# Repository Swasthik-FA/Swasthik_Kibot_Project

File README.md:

<h1 align="center">Board Name</h1>

<p align="center" width="100%">
  
</p>

***

<p align="center">
  
&nbsp; &nbsp; &nbsp; &nbsp;
  
</p>

***

## SPECIFICATIONS

| Parameter | Value | 
| --- | --- |
| Dimensions | 106.58 × 54.37 mm |

***

## DIRECTORY STRUCTURE

    .
    ├─ Computations       # Misc calculations
    ├─ HTML               # HTML files for generated webpage
    ├─ Images             # Pictures and renders
    │
    ├─ kibot_resources    # External resources for KiBot
    │  ├─ colors          # Color theme for KiCad
    │  ├─ fonts           # Fonts used in the project
    │  ├─ scripts         # External scripts used with KiBot
    │  └─ templates       # Templates for KiBot generated reports
    │
    ├─ kibot_yaml         # KiBot YAML config files
    ├─ KiRI               # KiRI (PCB diff viewer) files
    │
    ├─ lib                # KiCad footprint and symbol libraries
    │  ├─ 3d_models       # Component 3D models
    │  ├─ lib_fp          # Footprint libraries
    │  └─ lib_sym         # Symbol libraries
    │
    ├─ Logos              # Logos
    │
    ├─ Manufacturing      # Assembly and fabrication documents
    │  ├─ Assembly        # Assembly documents (BoM, pos, notes)
    │  │
    │  └─ Fabrication     # Fabrication documents (ZIP, notes)
    │     ├─ Drill Tables # CSV drill tables
    │     └─ Gerbers      # Gerbers
    │
    ├─ Report             # Reports for ERC/DRC
    ├─ Schematic          # PDF of schematic
    ├─ Templates          # Title block templates
    ├─ Testing
    │  └─ Testpoints      # Testpoints tables      
    │
    └─ Variants           # Outputs for assembly variants

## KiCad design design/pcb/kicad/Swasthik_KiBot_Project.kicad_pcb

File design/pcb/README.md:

# design/pcb/

This is the main working area for the PCB. Everything related to the circuit board lives under this directory.

See `../../FAQ.md` for the file-location lookup table and detailed Q&A.

## What's pre-created

Only two subdirectories are created by the template:

| Folder | Why it's pre-created |
|---|---|
| `kicad/` | KiCad project files go here. The shell scripts default to `design/pcb/kicad/Swasthik_KiBot_Project.kicad_pro` and related paths. |
| `outputs/` | Scripts write generated reports (ERC, DRC, BOM, schematic PDF) here. CI reads from here. |
| `reviews/` | Completed gate checklists land here as the project progresses through the 5 quality gates. |

## What to create when you need it

Everything else is created on demand. The template deliberately does not pre-materialize empty folders, because most projects will not use all of them. Create these as the work reaches that stage:

| Folder | When to create |
|---|---|
| `kicad/libraries/symbols/` | When you draw your first project-local schematic symbol |
| `kicad/libraries/footprints.pretty/` | When you create your first project-local footprint (note: `.pretty` suffix is mandatory — KiCad convention) |
| `kicad/libraries/3d/` | When you add your first project-local 3D model (STEP, WRL) |
| `datasheets/` | When you add your first component datasheet |
| `notes/` | When you start writing design notes (power tree calc, placement rationale, etc.) |
| `ecos/` | When the first Engineering Change Order happens (after prototype fabrication) |
| `outputs/review_pack/` | When you run `../../scripts/export_review_pack.sh` for the first time |
| `reviews/g1_specification_lock/`, `g2_schematic_review/`, etc. | When each gate is passed and the completed checklist is archived |
| `../mechanical/` | If the project has mechanical constraints (enclosure STEP, DXF) |
| `simulation/` | If you run simulation (LTspice, ngspice) |
| `references/` | If you collect app notes, reference designs, or competitor teardowns |

## The rule

**If a file describes the PCB, it lives under `design/pcb/`.** Source files, libraries, datasheets, generated outputs, review evidence, change orders — all here. The only exceptions are: (1) per-revision release packs at `release/`, and (2) project-level config at the repo root (`project_config.md`, etc.).

## Related files

- `../../README.md` — overall template guide
- `../../FAQ.md` — file-location lookup and Q&A (creating folders on demand is covered in section 2)
- `../../CLAUDE.md` — AI context for this repo

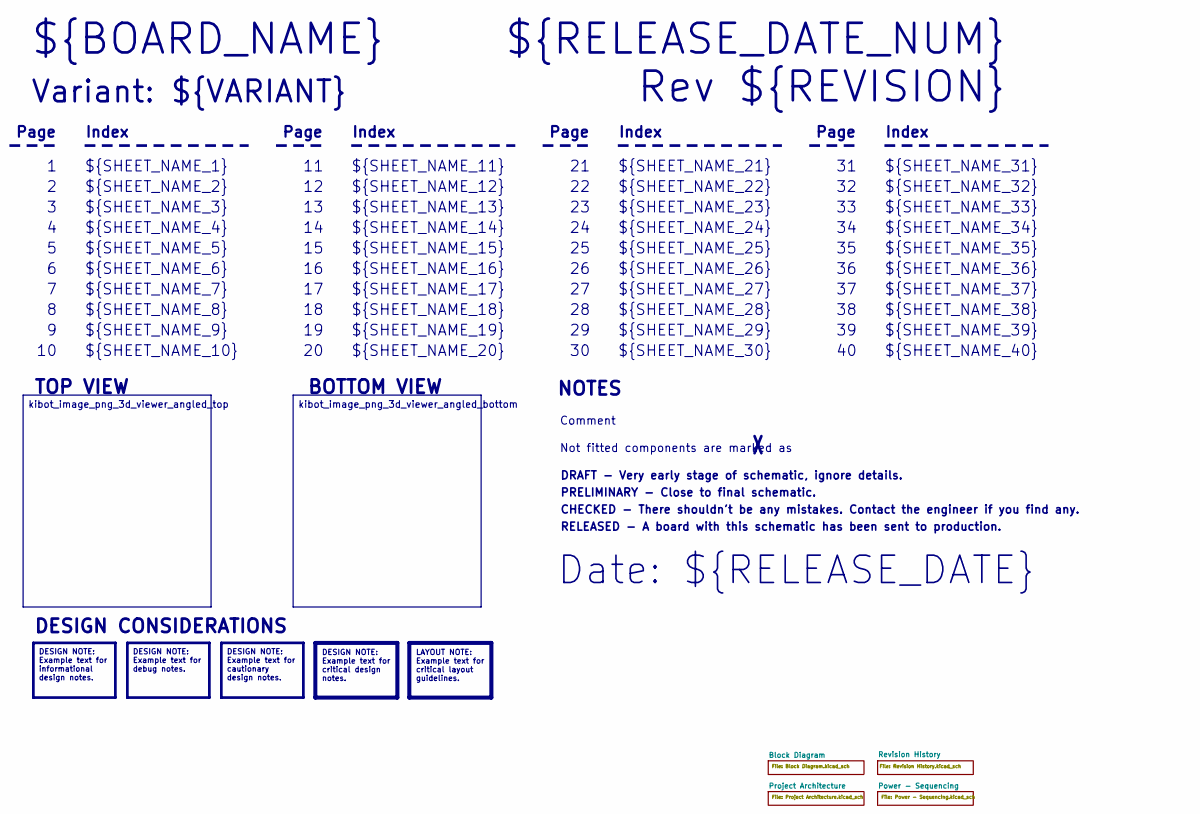
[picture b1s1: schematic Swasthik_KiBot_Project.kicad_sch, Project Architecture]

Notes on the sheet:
Variant: ${VARIANT}
RELEASED - A board with this schematic has been sent to production.
${SHEET_NAME_24}
Index
Page
PRELIMINARY - Close to final schematic.
${SHEET_NAME_22}
DRAFT - Very early stage of schematic, ignore details.
${SHEET_NAME_12}
${SHEET_NAME_8}
${SHEET_NAME_2}
${SHEET_NAME_5}
${SHEET_NAME_20}
${SHEET_NAME_23}
${RELEASE_DATE_NUM}
${SHEET_NAME_35}
Not fitted components are marked as
${SHEET_NAME_11}
${SHEET_NAME_6}
${SHEET_NAME_37}
${SHEET_NAME_26}
${SHEET_NAME_36}
Rev ${REVISION}
${SHEET_NAME_15}
CHECKED - There shouldn't be any mistakes. Contact the engineer if you find any.
BOTTOM VIEW
${SHEET_NAME_14}
${SHEET_NAME_21}
${SHEET_NAME_17}
${SHEET_NAME_18}
Date: ${RELEASE_DATE}
${SHEET_NAME_7}
${SHEET_NAME_31}
${BOARD_NAME}
NOTES
${SHEET_NAME_40}
${SHEET_NAME_39}
${SHEET_NAME_32}
${SHEET_NAME_1}
${SHEET_NAME_9}

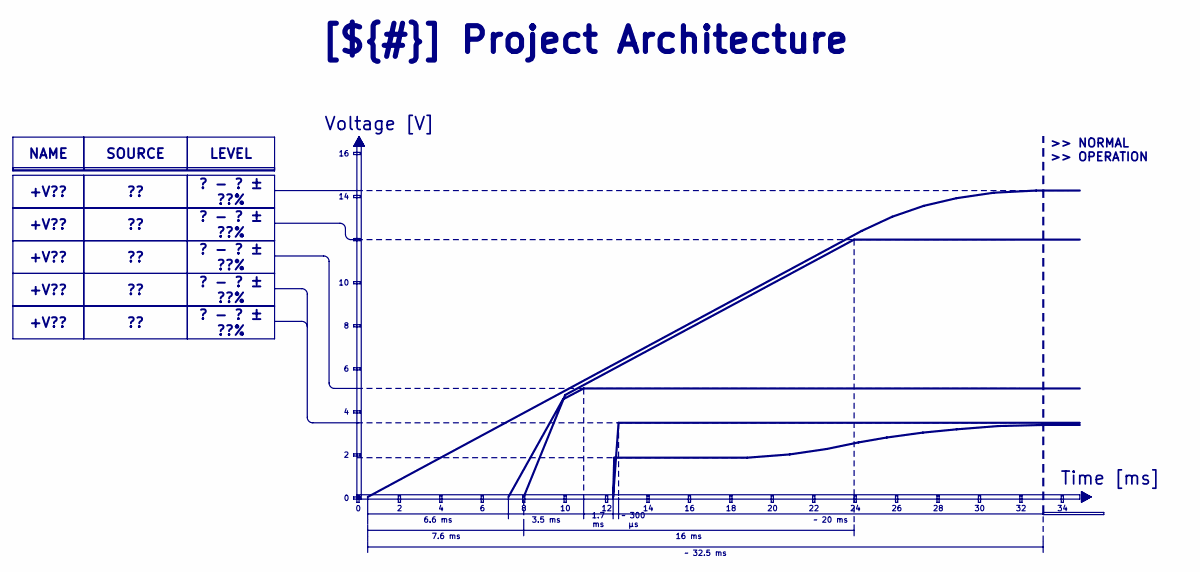
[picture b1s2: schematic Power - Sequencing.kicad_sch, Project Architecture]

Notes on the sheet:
Voltage [V]
>> NORMAL >> OPERATION
Time [ms]
3.5 ms
7.6 ms
? - ? ± ??%
~ 300 μs
1.7 ms
16 ms
+V??
LEVEL
NAME
~ 20 ms
SOURCE
[${#}] ${TITLE}
6.6 ms
~ 32.5 ms

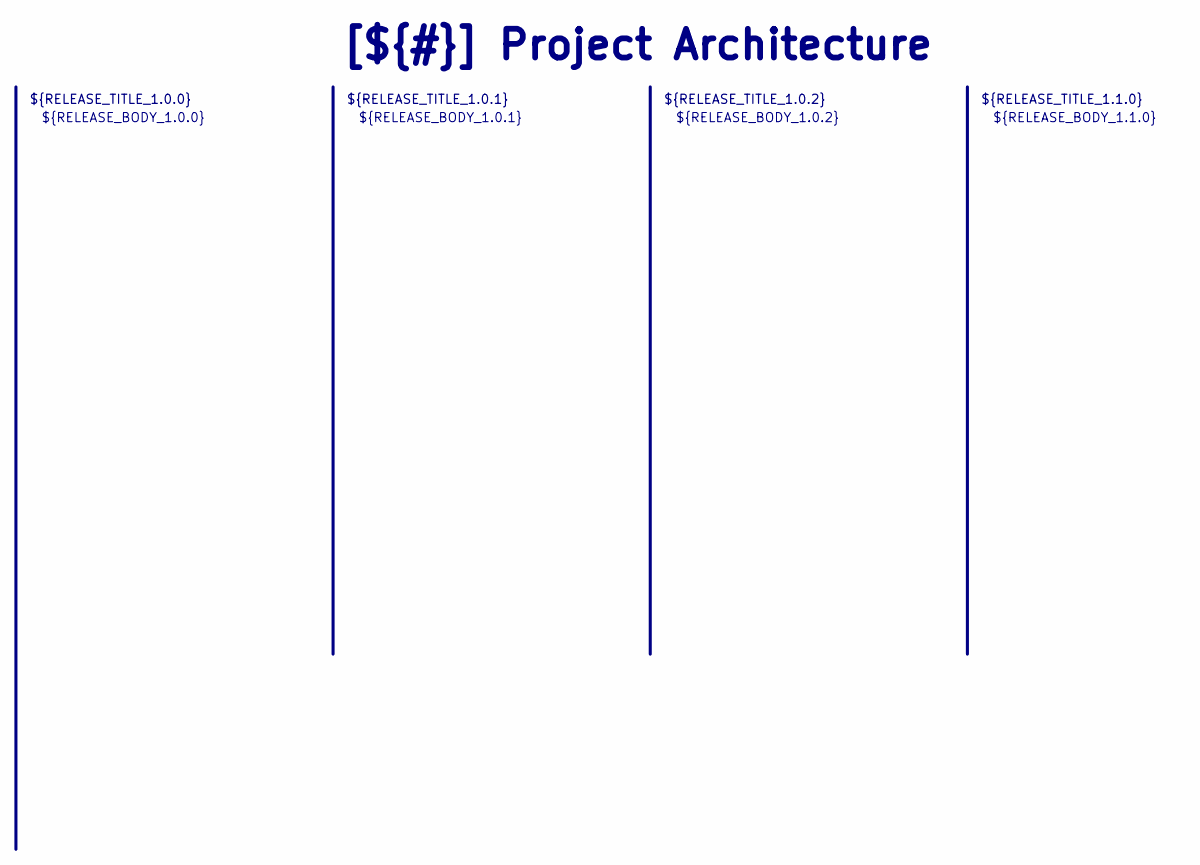
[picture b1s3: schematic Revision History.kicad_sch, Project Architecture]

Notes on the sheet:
${RELEASE_BODY_1.1.0}
[${#}] ${TITLE}
${RELEASE_BODY_1.0.0}
${RELEASE_TITLE_1.0.2}
${RELEASE_BODY_1.0.2}
${RELEASE_BODY_1.0.1}
${RELEASE_TITLE_1.0.0}
${RELEASE_TITLE_1.0.1}
${RELEASE_TITLE_1.1.0}

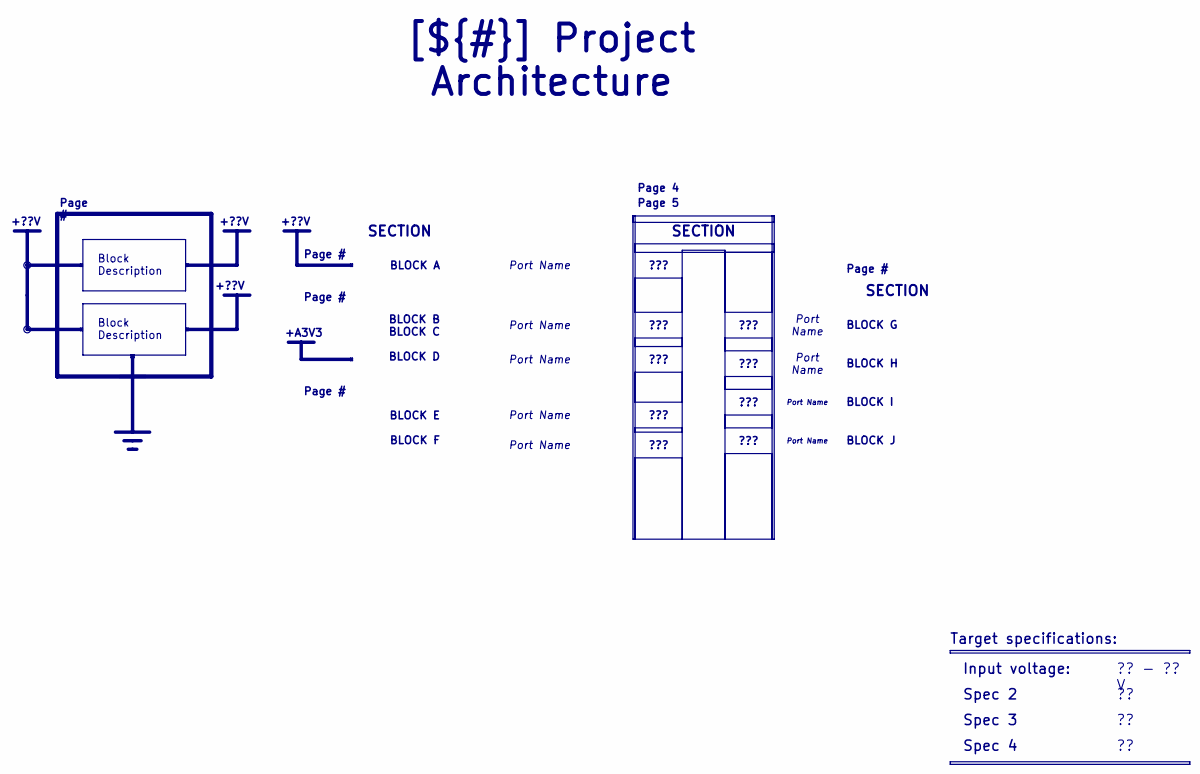
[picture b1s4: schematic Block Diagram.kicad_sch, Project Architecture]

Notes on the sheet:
+??V
+A3V3
SECTION
Spec 4
BLOCK H
BLOCK B BLOCK C BLOCK D
BLOCK I
?? - ?? V
Block Description
???
Port Name
BLOCK G
Page #
Page 4
[${#}] ${TITLE}
Input voltage:
Target specifications:
Spec 3
Spec 2
BLOCK A
BLOCK E BLOCK F
BLOCK J
Page 5

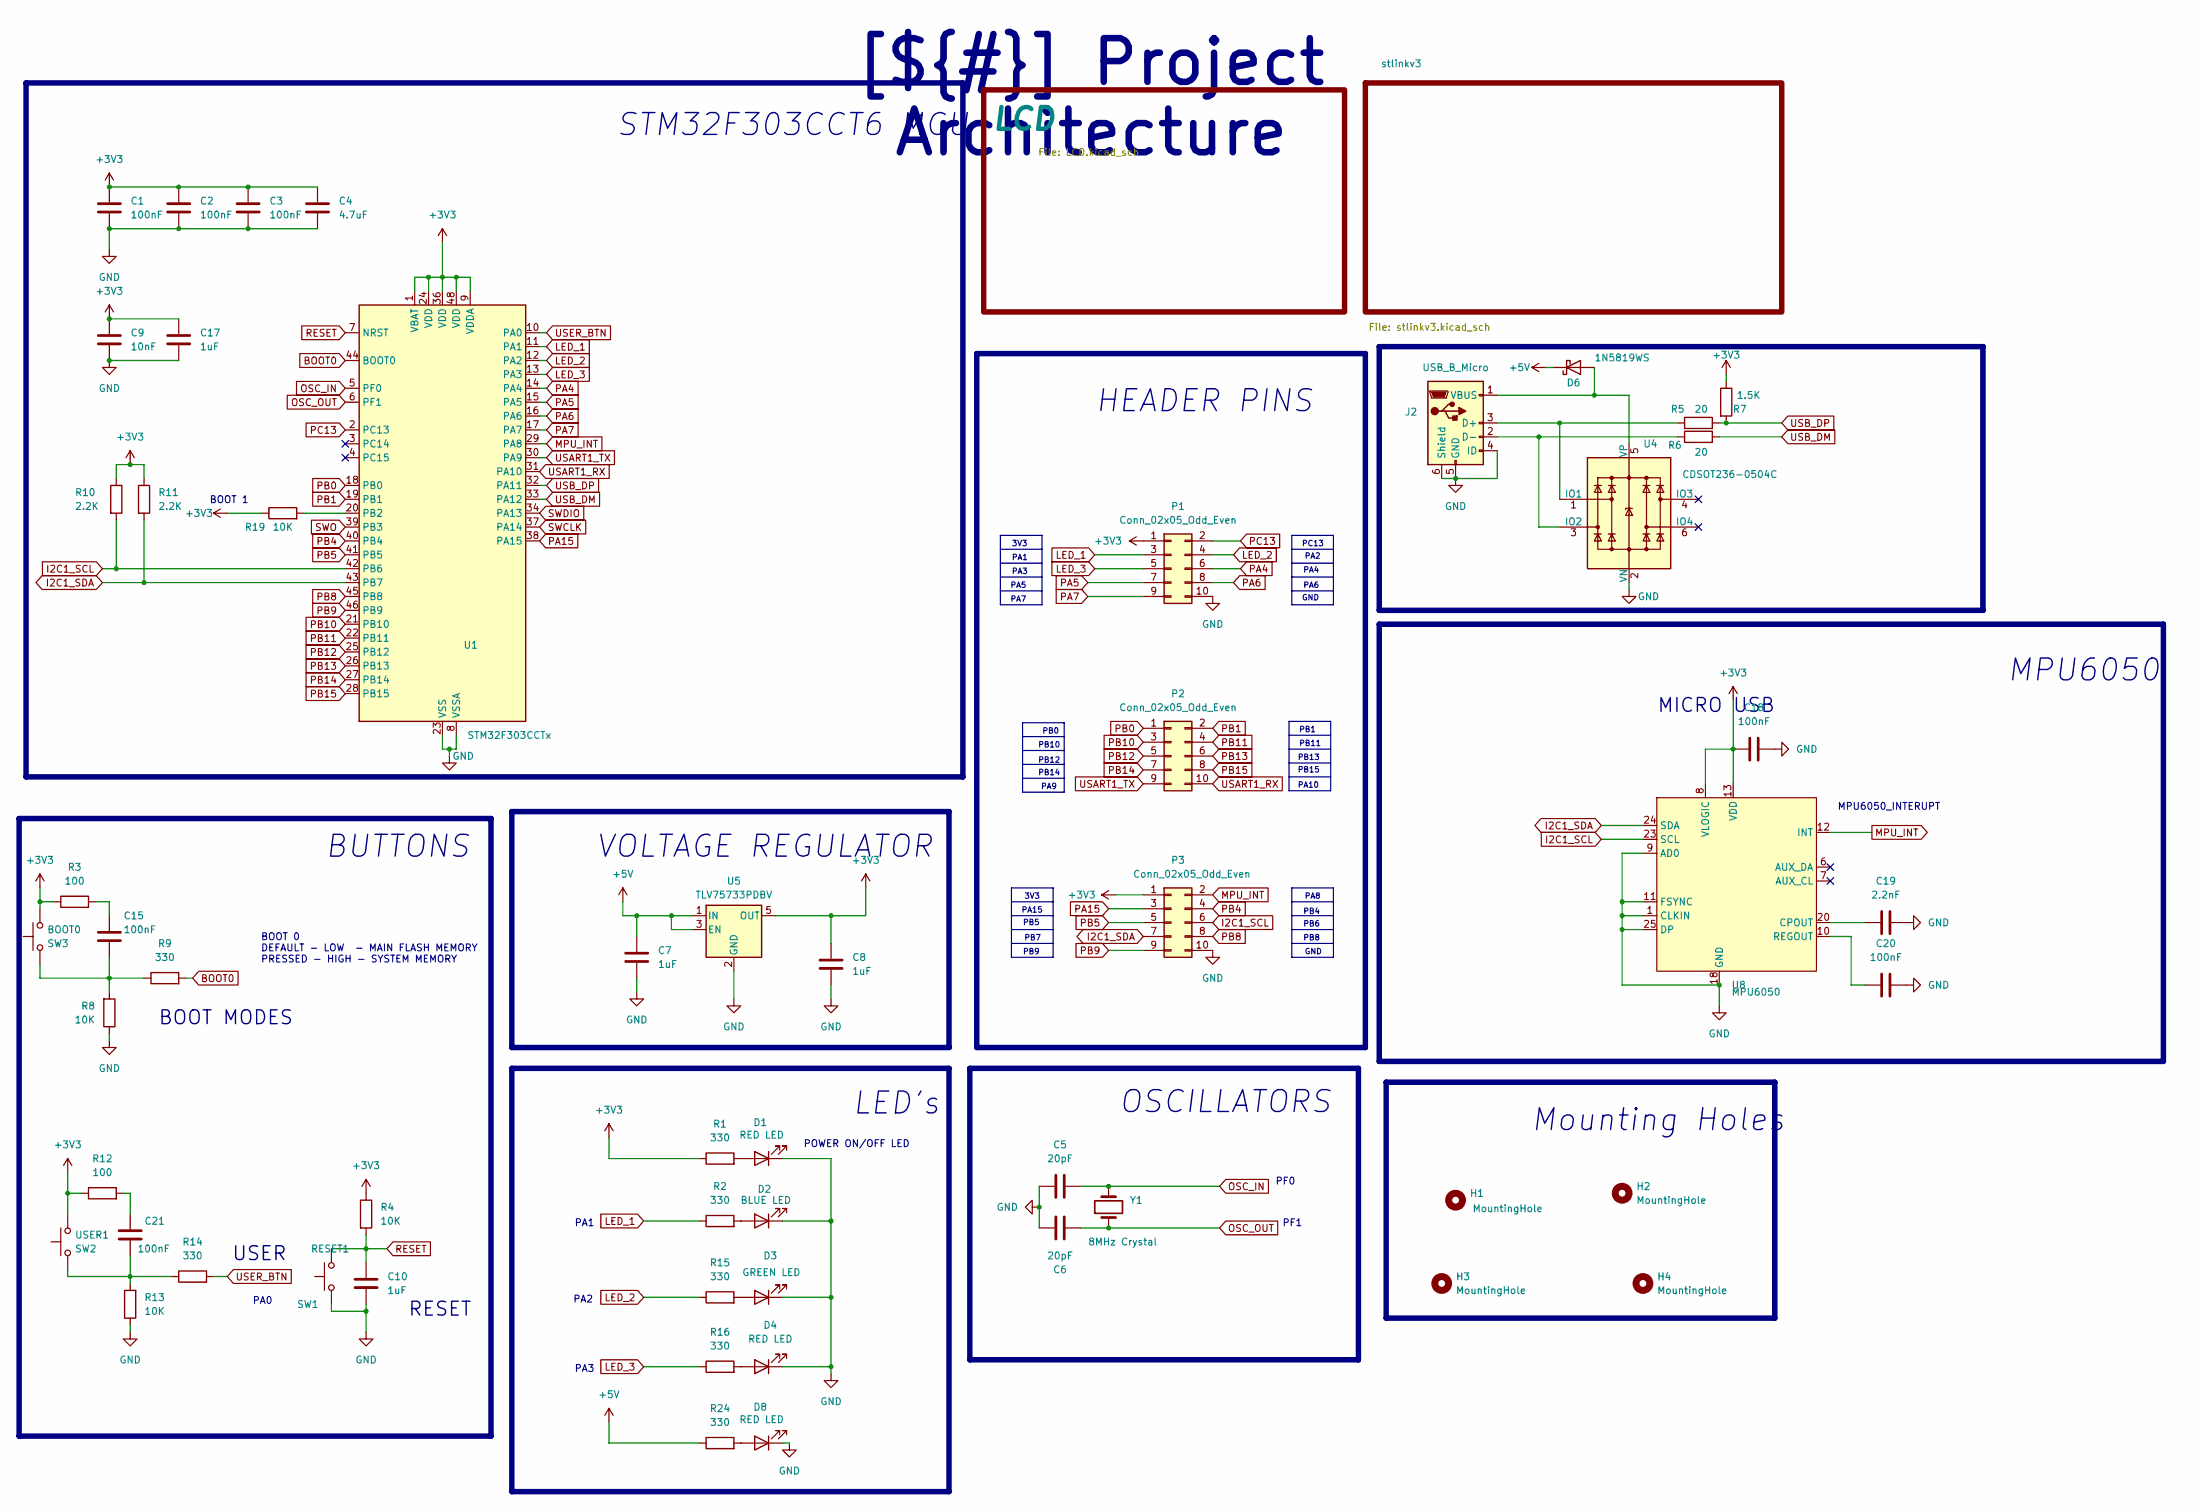
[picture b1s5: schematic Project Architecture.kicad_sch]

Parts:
BOOT0: SW3; SW_Tactile_SPST_NO_Straight_CK_PTS636Sx25SMTRLFS; MPN TS1101-C-W; LCSC C318938
C1, C2, C3, C15, C18, C20, C21: 100nF; C_0402_1005Metric; MPN TCC0402X5R1 04Z160A; LCSC C48579247
C4: 4.7uF; C_0402_1005Metric; MPN TCC0402X5R4 75M6R3AT; LCSC C48579247
C5, C6: 20pF; C_0402_1005Metric; MPN 0402CG200J50 0NT; LCSC C1554
C7, C8: 1uF; C_0402_1005Metric; LCSC C7503519
C9: 10nF; C_0402_1005Metric; MPN CC0402KRX7R9BB; LCSC C60133
C10, C17: 1uF; C_0402_1005Metric; MPN CL05A105KP5NNNC; LCSC C7503519
C19: 2.2nF; C_0402_1005Metric; MPN 0402B222K500CT; LCSC C338130
D1, D4, D8: RED LED; LED_0603_1608Metric; MPN BLHUB37A-AV-TRB; LCSC C165980
D2: BLUE LED; LED_0603_1608Metric; MPN BLHB337A-AV-TRB; LCSC C165977
D3: GREEN LED; LED_0603_1608Metric; MPN SZYY0402YG; LCSC C434449
D6: 1N5819WS; D_SOD-323; LCSC C191023
H1, H2, H3, H4: MountingHole; MountingHole_2.2mm_M2
J2: USB_B_Micro; micro_USB; MPN KH2.54FH1X12P-H8.5; LCSC C25503144
P1, P2, P3: Conn_02x05_Odd_Even; PinSocket_2x05_P2.54mm_Vertical_SMD; MPN 2.54-2*5P; LCSC C843271
R1, R2, R9, R14, R15, R16, R24: 330; R_0402_1005Metric; MPN FRC0402J331 TS; LCSC C2906929
R3, R12: 100; R_0402_1005Metric; MPN SCR0402J100R; LCSC C3017466
R4: 10K; R_0402_1005Metric; MPN SCR0402J100K; LCSC C51035904
R5, R6: 20; R_0402_1005Metric; MPN RC0402FR-0720RL; LCSC C138031
R7: 1.5K; R_0402_1005Metric; MPN FRC0402J152TS; LCSC C2929900
R8, R13, R19: 10K; R_0402_1005Metric; MPN SCR0402F10K; LCSC C51035904
R10, R11: 2.2K; R_0402_1005Metric; MPN CR0402FF2201G; LCSC C100309
RESET1: SW1; SW_Tactile_SPST_NO_Straight_CK_PTS636Sx25SMTRLFS; MPN TS1101-C-W; LCSC C318938
U1: STM32F303CCTx; LQFP-48_7x7mm_P0.5mm; MPN STM32F303CC T6; LCSC C81523
U4: CDSOT236-0504C; SOT-23-6; MPN CDSOT236- 0504C; LCSC C41409337
U5: TLV75733PDBV; SOT-23-5; LCSC C485517
U8: MPU6050; QFN-24-1EP_4x4mm_P0.5mm_EP2.7x2.6mm; MPN MPU-6050
USER1: SW2; SW_Tactile_SPST_NO_Straight_CK_PTS636Sx25SMTRLFS; MPN TS1101-C-W; LCSC C318938
Y1: 8MHz Crystal; Crystal_SMD_HC49-SD; MPN X49SM8MSD2; LCSC C12674

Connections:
+3V3: BOOT0.2, C1.1, C2.1, C3.1, C4.1, C8.1, C9.1, C17.1, C18.1, P1.1, P3.1, R1.1, R3.1, R4.1, R7.1, R10.1, R11.1, R12.1, R19.1, U1.1 (VBAT), U1.9 (VDDA), U1.24 (VDD), U1.36 (VDD), U1.48 (VDD), U5.5 (OUT), U8.8 (VLOGIC), U8.13 (VDD), USER1.2; also elsewhere on the board
+5V: C7.1, D6.1 (K), R24.1, U5.1 (IN), U5.3 (EN); also elsewhere on the board
BOOT0: R9.2, U1.44 (BOOT0)
GND: C1.2, C2.2, C3.2, C4.2, C5.1, C6.1, C7.2, C8.2, C9.2, C10.2, C17.2, C18.2, C19.2, C20.2, D1.1 (K), D2.1 (K), D3.1 (K), D4.1 (K), D8.1 (K), J2.4 (ID), J2.5 (GND), J2.6 (Shield), P1.10, P3.10, R8.1, R13.1, RESET1.1, U1.8 (VSSA), U1.23 (VSS), U1.35 (VSS), U1.47 (VSS), U4.2 (VN), U5.2 (GND), U8.1 (CLKIN), U8.9 (AD0), U8.11 (FSYNC), U8.18 (GND), U8.25 (DP); also elsewhere on the board
I2C1_SCL: P3.6, R10.2, U1.42 (PB6), U8.23 (SCL)
I2C1_SDA: P3.7, R11.2, U1.43 (PB7), U8.24 (SDA)
LED_1: P1.3, R2.1, U1.11 (PA1)
LED_2: P1.4, R15.1, U1.12 (PA2)
LED_3: P1.5, R16.1, U1.13 (PA3)
MPU_INT: P3.2, U1.29 (PA8), U8.12 (INT)
unnamed: BOOT0.1, C15.2, R8.2, R9.1
unnamed: C15.1, R3.2
unnamed: C21.1, R12.2
unnamed: C21.2, R13.2, R14.1, USER1.1
unnamed: D1.2 (A), R1.2
unnamed: D2.2 (A), R2.2
unnamed: D3.2 (A), R15.2
unnamed: D4.2 (A), R16.2
unnamed: D6.2 (A), J2.1 (VBUS), U4.5 (VP)
unnamed: D8.2 (A), R24.2
unnamed: J2.3 (D+), R5.1, U4.1 (IO1)
unnamed: J2.2 (D-), R6.1, U4.3 (IO2)
unnamed: R19.2, U1.20 (PB2)
unnamed: C19.1, U8.20 (CPOUT)
unnamed: C20.1, U8.10 (REGOUT)
OSC_IN: C5.2, U1.5 (PF0), Y1.2
OSC_OUT: C6.2, U1.6 (PF1), Y1.1
PA4: P1.6, U1.14 (PA4)
PA5: P1.7, U1.15 (PA5)
PA6: P1.8, U1.16 (PA6)
PA7: P1.9, U1.17 (PA7)
PA15: P3.3, U1.38 (PA15)
PB0: P2.1, U1.18 (PB0)
PB1: P2.2, U1.19 (PB1)
PB4: P3.4, U1.40 (PB4)
PB5: P3.5, U1.41 (PB5)
PB8: P3.8, U1.45 (PB8)
PB9: P3.9, U1.46 (PB9)
PB10: P2.3, U1.21 (PB10)
PB11: P2.4, U1.22 (PB11)
PB12: P2.5, U1.25 (PB12)
PB13: P2.6, U1.26 (PB13)
PB14: P2.7, U1.27 (PB14)
PB15: P2.8, U1.28 (PB15)
PC13: P1.2, U1.2 (PC13)
RESET: C10.1, R4.2, RESET1.2, U1.7 (NRST); also elsewhere on the board
SWCLK: U1.37 (PA14); also elsewhere on the board
SWDIO: U1.34 (PA13); also elsewhere on the board
SWO: U1.39 (PB3); also elsewhere on the board
USART1_RX: P2.10, U1.31 (PA10); also elsewhere on the board
USART1_TX: P2.9, U1.30 (PA9); also elsewhere on the board
USB_DM: R6.2, U1.33 (PA12)
USB_DP: R5.2, R7.2, U1.32 (PA11)
USER_BTN: R14.2, U1.10 (PA0)

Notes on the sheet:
STM32F303CCT6 MCU
BOOT MODES
PB14
PB1
3V3
BOOT 0 DEFAULT - LOW - MAIN FLASH MEMORY PRESSED - HIGH - SYSTEM MEMORY
PA15
MPU6050
PA1
VOLTAGE REGULATOR
PB11
PF1
PF0
PB7
HEADER PINS
BUTTONS
PA3
PB12
PA6
PB5
PA8
MPU6050_INTERUPT
PB0
PB9
PB4
PA2
POWER ON/OFF LED
PB6
PB13
MICRO USB
PA5
PA9
GND
RESET
PA10
PC13
LED's
PA0
PB10
Mounting Holes

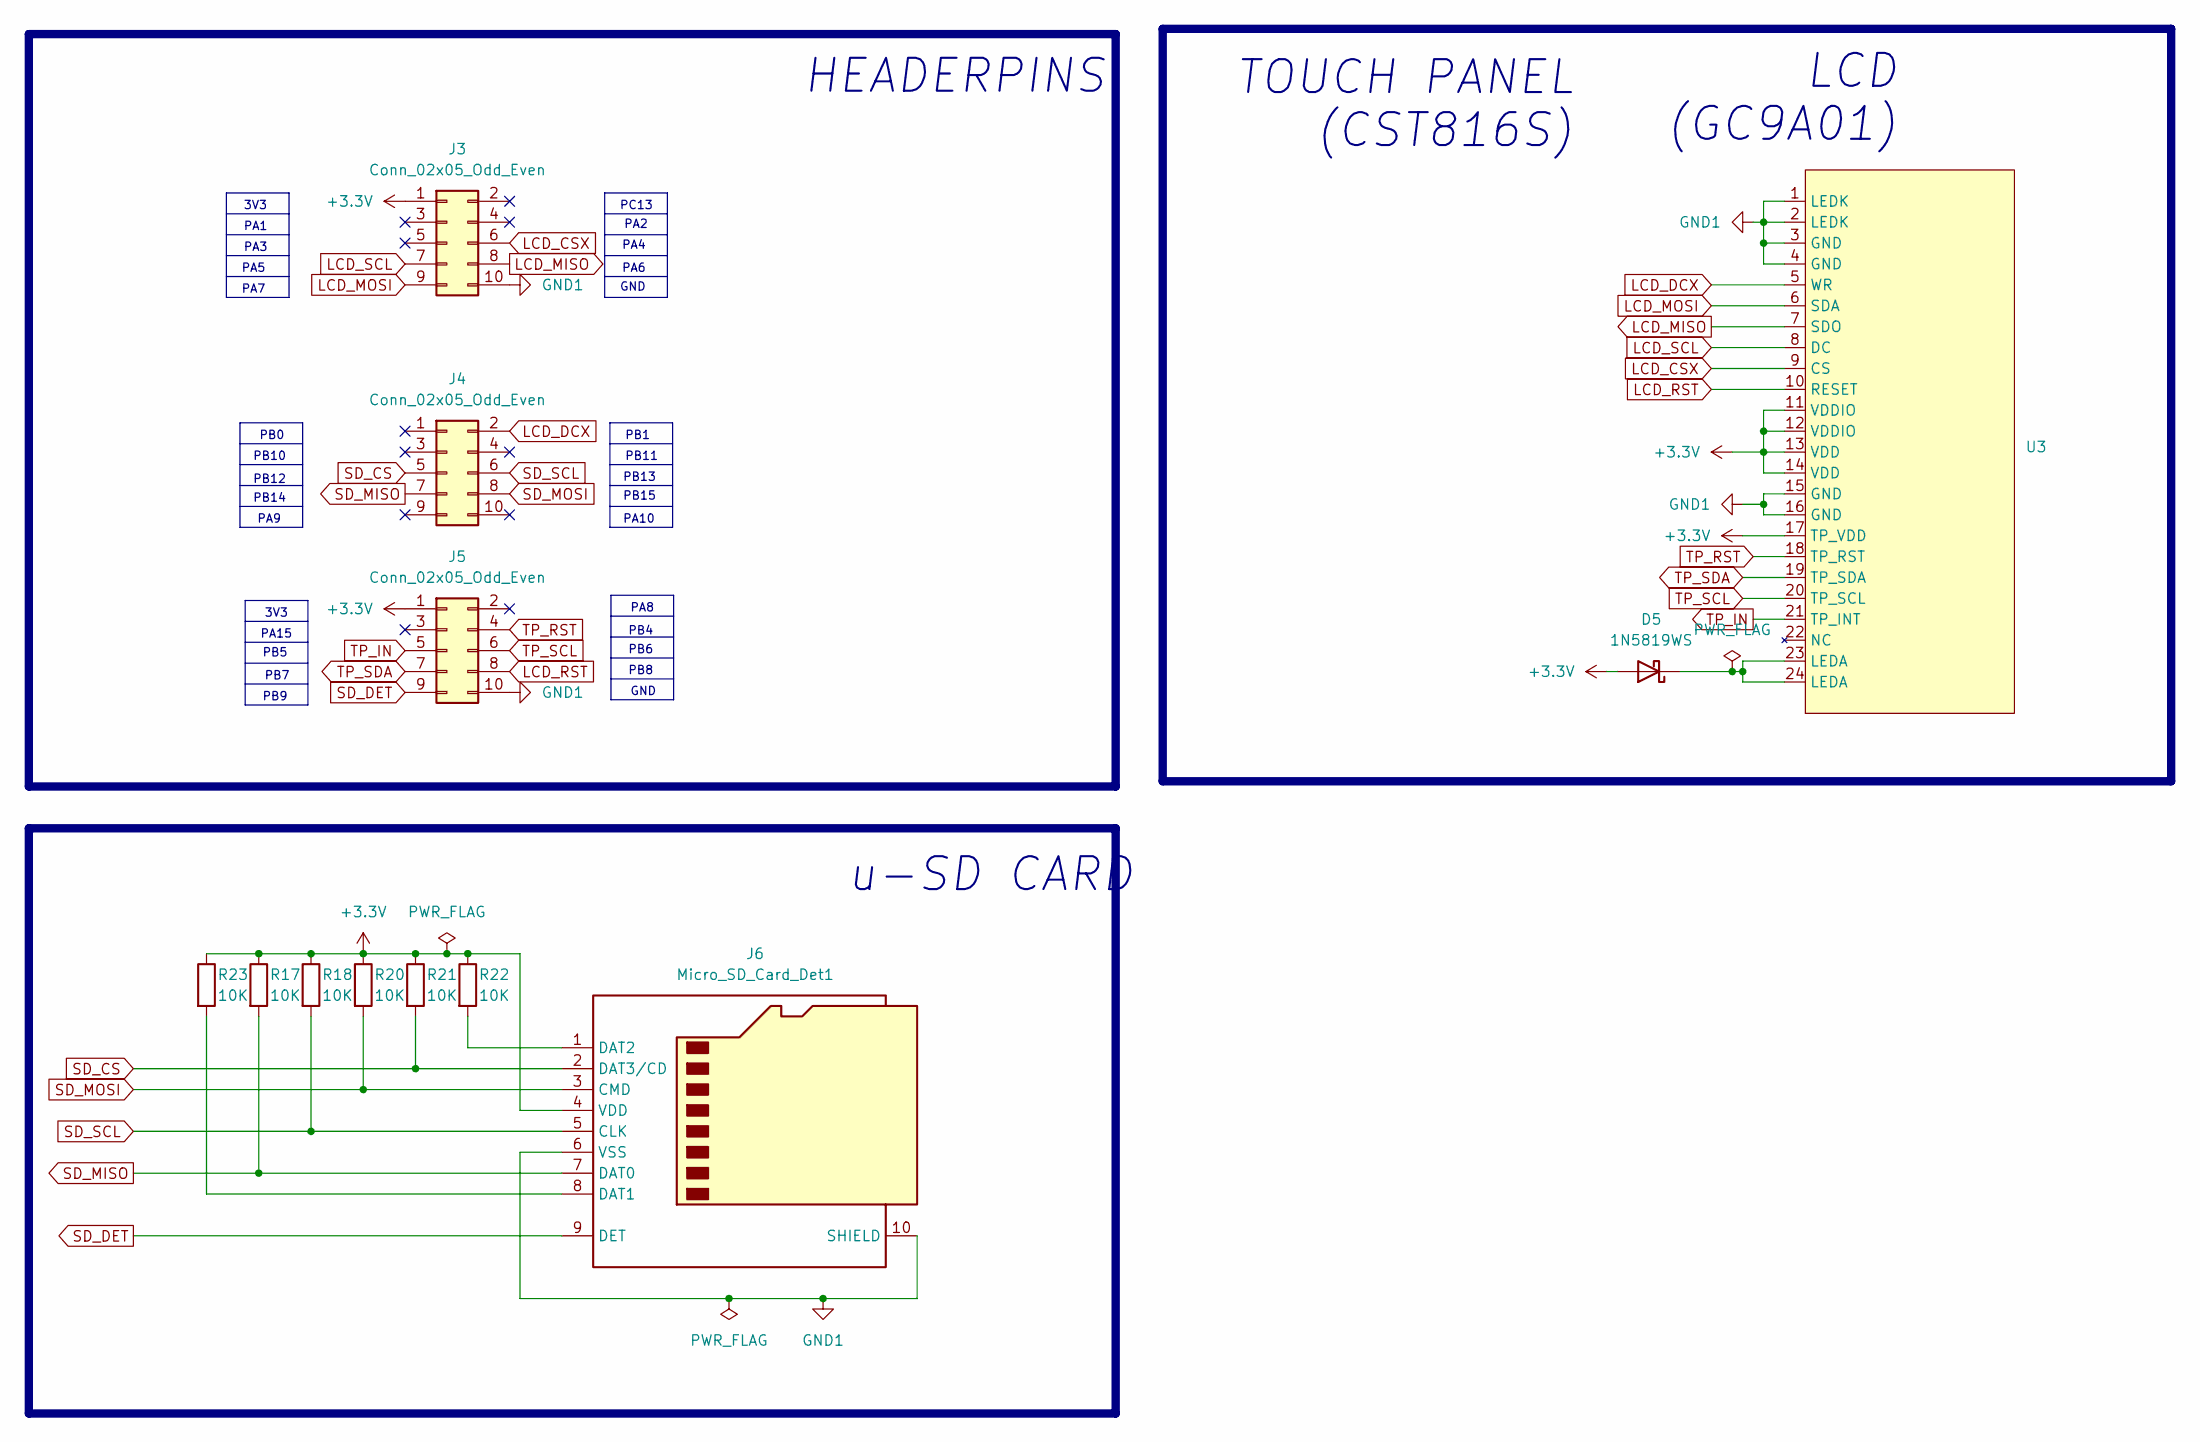
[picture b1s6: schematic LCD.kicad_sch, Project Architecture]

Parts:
D5: 1N5819WS; D_SOD-123; LCSC C191023
J3, J4, J5: Conn_02x05_Odd_Even; PinHeader_2x05_P2.54mm_Vertical_SMD; MPN PZ254-2-05-S; LCSC C3294463
J6: Micro_SD_Card_Det1; CUI_MSD-1-A; MPN MLD-TF PUSH-H18; LCSC C52750848
R17, R18, R20, R21, R22, R23: 10K; R_0402_1005Metric; MPN SCR0402F10K; LCSC C51035904
U3: OK-24F024-04

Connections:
+3.3V: D5.2 (A), J3.1, J5.1, J6.4 (VDD), R17.1, R18.1, R20.1, R21.1, R22.1, R23.1, U3.11 (VDDIO), U3.12 (VDDIO), U3.13 (VDD), U3.14 (VDD), U3.17 (TP_VDD)
GND1: J3.10, J5.10, J6.6 (VSS), J6.10 (SHIELD), U3.1 (LEDK), U3.2 (LEDK), U3.3 (GND), U3.4 (GND), U3.15 (GND), U3.16 (GND)
LCD_CSX: J3.6, U3.9 (CS)
LCD_DCX: J4.2, U3.5 (WR)
LCD_MISO: J3.8, U3.7 (SDO)
LCD_MOSI: J3.9, U3.6 (SDA)
LCD_RST: J5.8, U3.10 (RESET)
LCD_SCL: J3.7, U3.8 (DC)
unnamed: D5.1 (K), U3.23 (LEDA), U3.24 (LEDA)
unnamed: J6.8 (DAT1), R23.2
unnamed: J6.1 (DAT2), R22.2
SD_CS: J4.5, J6.2 (DAT3/CD), R21.2
SD_DET: J5.9, J6.9 (DET)
SD_MISO: J4.7, J6.7 (DAT0), R17.2
SD_MOSI: J4.8, J6.3 (CMD), R20.2
SD_SCL: J4.6, J6.5 (CLK), R18.2
TP_IN: J5.5, U3.21 (TP_INT)
TP_RST: J5.4, U3.18 (TP_RST)
TP_SCL: J5.6, U3.20 (TP_SCL)
TP_SDA: J5.7, U3.19 (TP_SDA)

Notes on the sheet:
PA15
LCD (GC9A01)
PB7
PA6
PB11
PB14
PA9
3V3
PB6
PB9
PB4
PA1
PB5
GND
PB10
u-SD CARD
HEADERPINS
PB15
PB13
PB0
PB12
TOUCH PANEL (CST816S)
PA3
PA4
PA8
PA2
PA10
PA7
PA5
PB1
PB8
PC13

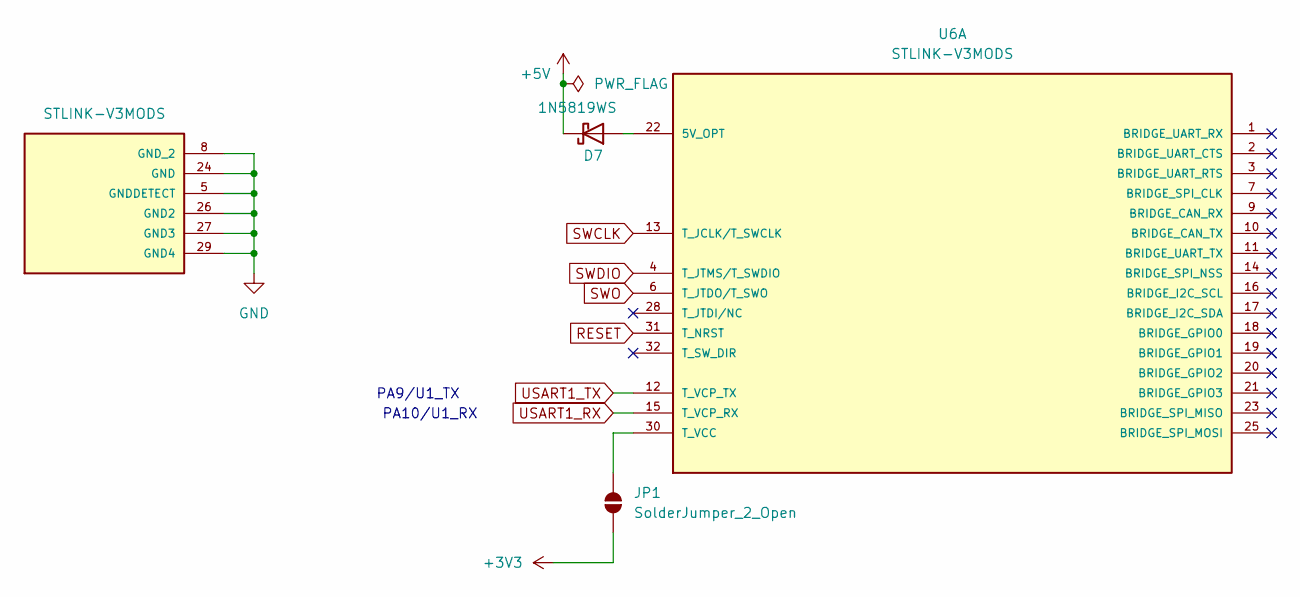
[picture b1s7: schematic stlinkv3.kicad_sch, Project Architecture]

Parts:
D7: 1N5819WS; D_SOD-323; LCSC C191023
JP1: SolderJumper_2_Open; SolderJumper-2_P1.3mm_Bridged_Pad1.0x1.5mm
U6: STLINK-V3MODS; MODULE_STLINK-V3MODS; PARTREV 1

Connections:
+3V3: JP1.1 (A); also elsewhere on the board
+5V: D7.1 (K); also elsewhere on the board
GND: U6.5 (GNDDETECT), U6.8 (GND_2), U6.24 (GND), U6.26 (GND2), U6.27 (GND3), U6.29 (GND4); also elsewhere on the board
unnamed: D7.2 (A), U6.22 (5V_OPT)
unnamed: JP1.2 (B), U6.30 (T_VCC)
RESET: U6.31 (T_NRST); also elsewhere on the board
SWCLK: U6.13 (T_JCLK/T_SWCLK); also elsewhere on the board
SWDIO: U6.4 (T_JTMS/T_SWDIO); also elsewhere on the board
SWO: U6.6 (T_JTDO/T_SWO); also elsewhere on the board
USART1_RX: U6.15 (T_VCP_RX); also elsewhere on the board
USART1_TX: U6.12 (T_VCP_TX); also elsewhere on the board

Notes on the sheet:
PA9/U1_TX
PA10/U1_RX

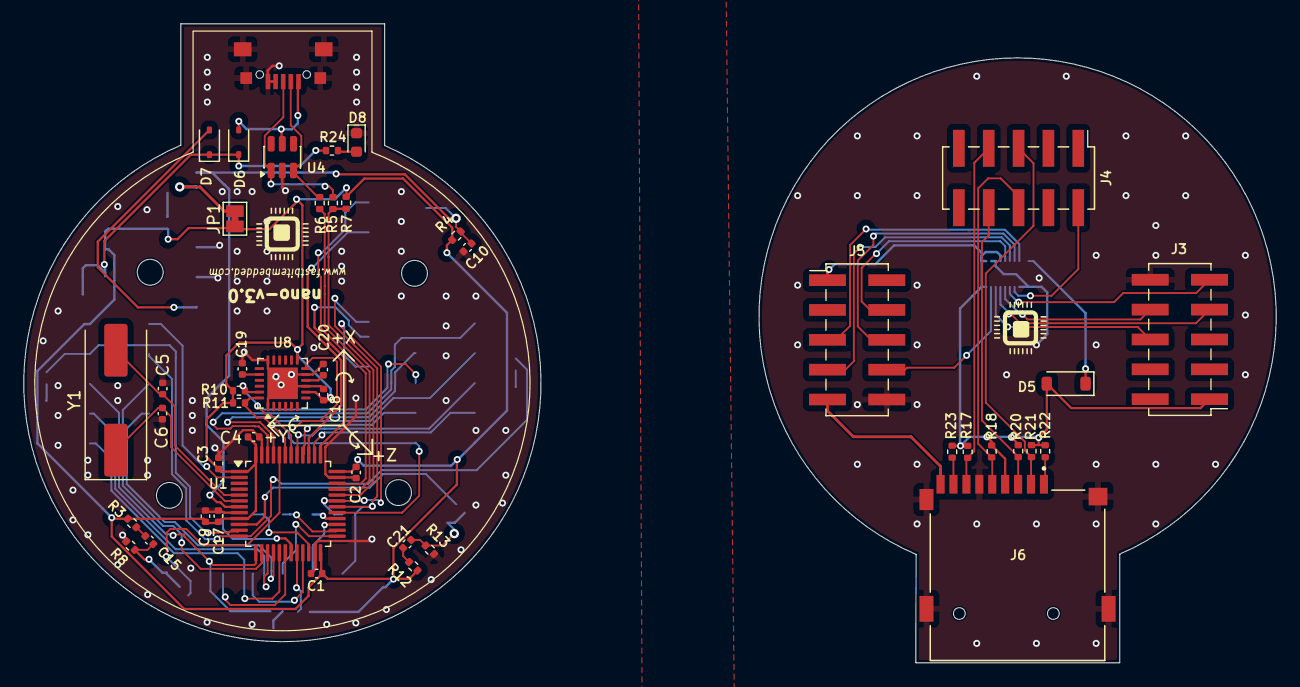
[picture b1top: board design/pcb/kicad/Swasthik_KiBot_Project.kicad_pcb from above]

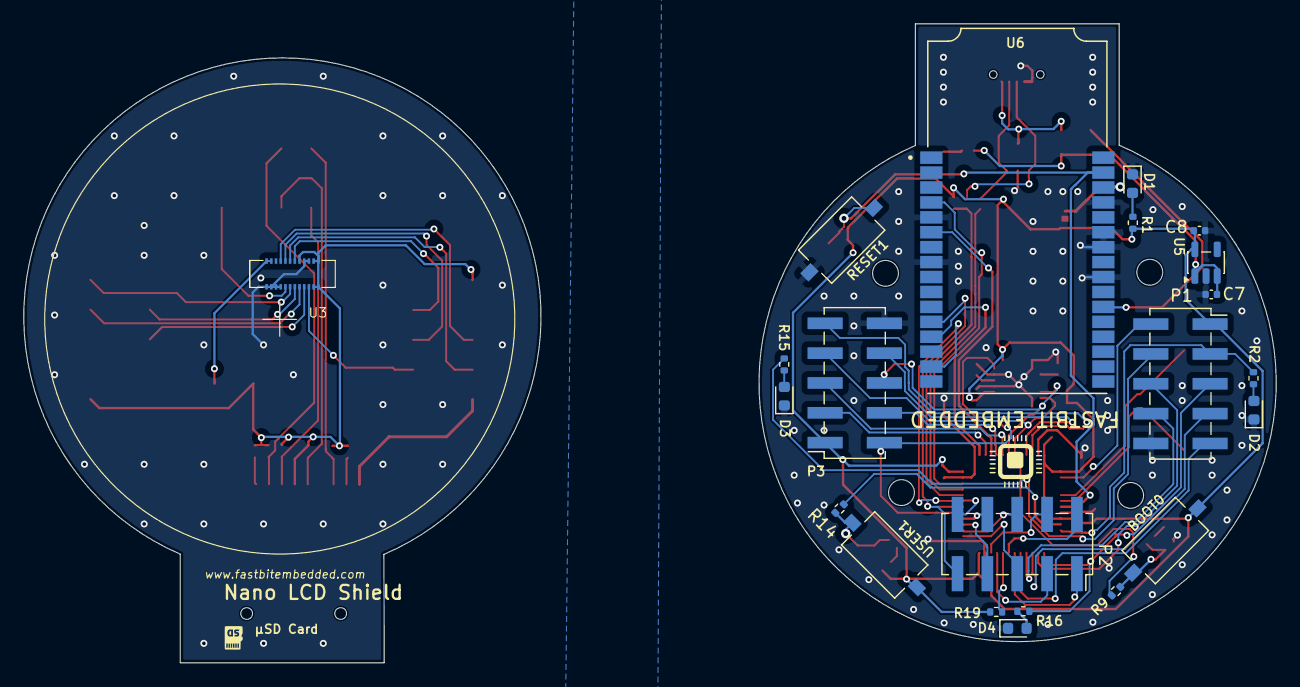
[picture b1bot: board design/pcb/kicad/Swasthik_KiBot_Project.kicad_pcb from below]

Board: 2 copper layers, 44.0 x 52.6 mm, 71 parts (26 on the bottom side), 76 nets.

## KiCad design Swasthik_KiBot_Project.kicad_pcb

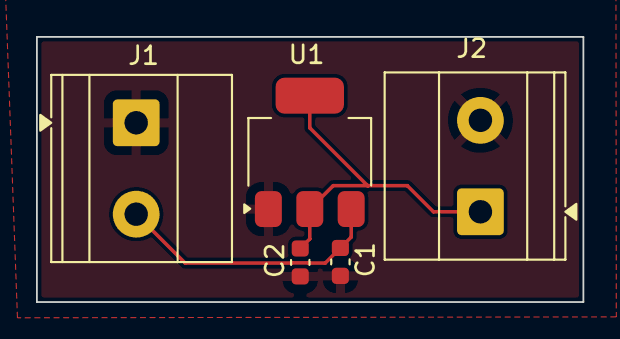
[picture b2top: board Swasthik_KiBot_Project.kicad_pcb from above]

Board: 2 copper layers, 30.4 x 14.7 mm, 5 parts (0 on the bottom side), 3 nets.

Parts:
C1, C2: 1uF; C_0603_1608Metric
J1, J2: Screw_Terminal_01x02; TerminalBlock_Phoenix_MKDS-1,5-2-5.08_1x02_P5.08mm_Horizont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
U1: NCP1117-3.3_SOT223; SOT-223-3_TabPin2

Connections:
GND: C1.2, C2.2, J1.1, J2.2, U1.1 (GND)
unnamed: C1.1, J1.2, U1.3 (VI)
unnamed: C2.1, J2.1, U1.2 (VO)

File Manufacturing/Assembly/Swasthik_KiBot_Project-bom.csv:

Row,Quantity Per PCB,References,Value,Datasheet,Footprint,Description,Manufacturer,Manufacturer Part Number,Supplier Part Number
1,2,C1 C2,1uF,~,C_0603_1608Metric,Unpolarized capacitor,,,
2,2,J1 J2,Screw_Terminal_01x02,~,"TerminalBlock_Phoenix_MKDS-1,5-2-5.08_1x02_P5.08mm_Horizontal","Generic screw terminal, single row, 01x02, script generated (kicad-library-utils/schlib/autogen/connector/)",,,
3,1,U1,NCP1117-3.3_SOT223,http://www.onsemi.com/pub_link/Collateral/NCP1117-D.PDF,SOT-223-3_TabPin2,"1A Low drop-out regulator, Fixed Output 3.3V, SOT-223",,,

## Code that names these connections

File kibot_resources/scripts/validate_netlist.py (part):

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            },

            # === USB (DS Section 6.1.10) ===
            # PA11 = USB_DM (D-), PA12 = USB_DP (D+) — per DS pinout table
            # STM32F303CC note: PA11 is D- (DM), PA12 is D+ (DP) — not swapped
            "PA11": {
                "must_not_float": True,
                "must_have_comp": "R",
                "description": "PA11 (USB_DM/D-) must connect to USB D- via series resistor",
            },
            "PA12": {
                "must_not_float": True,
                "must_have_comp": "R",
                "description": "PA12 (USB_DP/D+) must connect to USB D+ via series resistor",
            },

            # === SWD debug interface (DS Section 6.3.4) ===
            "PA13": {
                "must_not_float": True,
                "description": "PA13 (SWDIO) must connect to debug header or ST-Link",
            },
            "PA14": {
                "must_not_float": True,
                "description": "PA14 (SWCLK) must connect to debug header or ST-Link",
            },

            # === I2C (application-specific) ===
            "PB6": {
                "must_not_float": True,
                "must_have_comp": "R",
                "description": "PB6 (I2C1_SCL) requires pull-up resistor",
            },
            "PB7": {
                "must_not_float": True,
                "must_have_comp": "R",
                "description": "PB7 (I2C1_SDA) requires pull-up resistor",
            },
        },
        "global_checks": {
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
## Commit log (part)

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2026-04-13 Add LDO Schematic and Layout
2026-04-13 Update Outputs
2026-04-13 Change Draft To checked
2026-04-13 Update layout
2026-04-13 Add netlist validation script for datasheet-based connection checks
    - Add validate_netlist.py that parses KiCad netlist and validates
    component connections against user-defined datasheet rules
    - Add NCP1117-3.3V LDO rules: GND connection, input/output caps,
    cap-to-ground bridging, minimum capacitor values
    - Integrate validation step into CI/CD pipeline (runs for
    PRELIMINARY, CHECKED, and RELEASED variants)
2026-04-13 Add generic category-based validation rules and HTML report
    - Replace per-part-only validation with automatic category detection
    (voltage regulators, MCUs, ICs, crystals, connectors)
    - Components are matched by KiCad library name and keywords
    - Part-specific rules (NCP1117) still apply on top of generic rules
    - Generate HTML report with dark theme, expandable sections,
    color-coded pass/warn/fail badges
2026-04-13 Restructure project to gate-review folder layout
    - Move KiCad source files to design/pcb/kicad/
    - Move generated outputs to design/pcb/outputs/
    - Move ERC/DRC/validation reports to design/pcb/reports/
    - Add gate review directories (g1-g5) under design/pcb/reviews/
    - Add waivers, ecos, bring_up directories
    - Create gate_log.md, stackup.md, bring_up_plan.md, release_notes.md
2026-04-13 Fix CI: add schema and board paths for KiBot action
    KiBot action cannot auto-detect project files in subdirectories.
    Explicitly pass schema and board paths to all KiBot steps.
2026-04-13 Fix CI: move KiBot config back to repo root for path resolution
    KiBot command: directives run from the repo root, so kibot_yaml/,
    kibot_resources/, CHANGELOG.md, and kibot_launch.sh must be at
    root level. KiCad source files stay in design/pcb/kicad/.
    Output paths in kibot_main.yaml now use full paths from repo root.
    Removed dir parameter from CI - KiBot runs from repo root with
    explicit schema and board paths.
2026-04-13 Fix logo path after project restructure
    Update LOGO path from Logos/ to design/pcb/kicad/Logos/ since
    KiBot resolves paths from the repo root.
2026-04-13 Add LCD and STLink schematic sheets, update KiCad project files
2026-04-13 Update PCB layout and project settings
2026-04-14 Align git structure and CI/CD to SOP-HW-002
    - Add pcb-checks.yaml: blocking CI gate (ERC/DRC/BOM) per SOP Section 10
    Fails on errors only, warnings reported but don't block
    - Update ci.yaml: add qa branch trigger, hw-v* tag format, PR triggers,
    guard auto-commit steps to only run on push events
    - Add qa branch to three-branch model (dev -> qa -> main)
    - Add Fastbit PCB Design Mini SOP v1.0 document
2026-04-14 Restrict CI outputs to dev, add pcb-gate dependency, clean gitignore
    - ci.yaml: generate_outputs only on dev push + tags (removed qa/main)
    - ci.yaml: added pcb-gate job (ERC/DRC/BOM) that must pass before
    generate_outputs runs
    - ci.yaml: removed PR trigger (pcb-checks.yaml handles PR validation)
    - gitignore: added .claude/, *.xml, organized with comments
    - Untracked .claude/settings.local.json and KiCad BOM XML exports
2026-04-14 Add STM32F303CC datasheet rules to netlist validation
    - Added part-specific rules for STM32F303CCTx based on datasheet:
    - USB: PA11 (D-) and PA12 (D+) must have series resistors
    - SWD: PA13 (SWDIO) and PA14 (SWCLK) must be connected
    - Power: VDD/VDDA/VBAT must not float, require bypass caps
    - Ground: VSS/VSSA must connect to GND net
    - Reset: NRST requires 100nF filter cap
2026-04-14 Run pcb-checks on all branch pushes, not just dev/qa/main
    Feature branches now get ERC, DRC, BOM, and netlist validation
    on every push so errors are caught before opening a PR.
2026-04-14 Add pre-push hook for local PCB validation before push
    - hooks/pre-push: runs ERC, DRC, BOM export, and STM32 netlist
    validation locally before allowing any push
    - Blocks push if any errors found (warnings pass)
    - Auto-detects kicad-cli on Windows (KiCad 8/9 paths)
    - Install: git config core.hooksPath hooks
    - Reports saved to .pre-push-checks/ on failure
2026-04-14 Change of USB and STlink label
2026-04-14 Add gitignore
2026-04-15 My modified version
2026-04-28 New Component
